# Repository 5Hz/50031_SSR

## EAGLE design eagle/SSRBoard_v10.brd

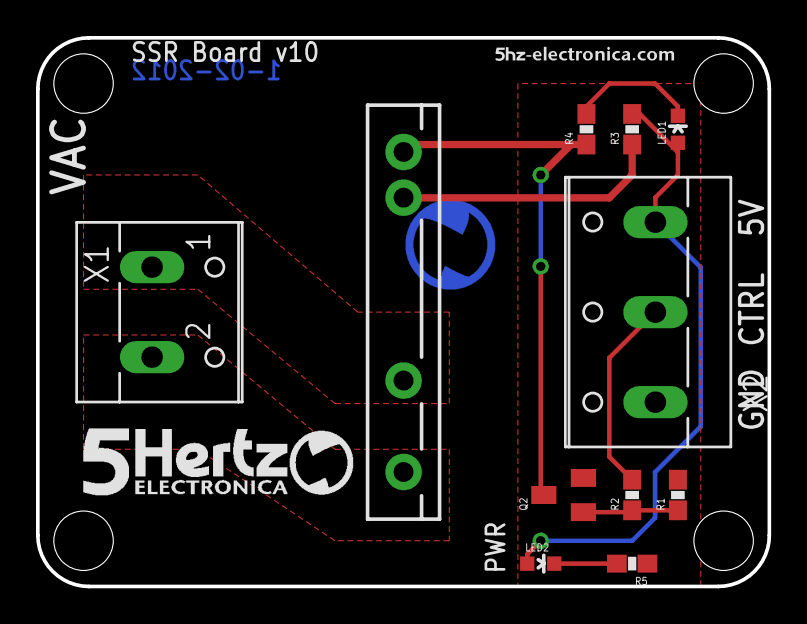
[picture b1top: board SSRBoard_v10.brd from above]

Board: 2 copper layers, 40.6 x 30.5 mm, 18 parts (1 on the bottom side), 10 nets.

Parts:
LED1, LED2: LED-0603
LOGO1: LOGO_5HZ_H_15MM; 5HZ_LOGO_H_15MM
LOGO2: LOGO_5HZ_WEB_COOPER_10MM; 5HZ_WEB_COOPER_10MM
LOGO4: LOGO_5HZ_CIRC_COOPER_5MM; 5HZ_LOGO_CIRC_COOPER_5MM
Q2: 2N3904; SOT23
R1: 10K; 0603-RES
R2, R4, R5: 330; 0603-RES
R3: 150; 0603-RES
U1: S108T02; RELAY-S108T02
U$3, U$4, U$5, U$7: STAND-OFF
X1: W237-102
X2: W237-103

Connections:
5V: LED1.A, LED2.A, R3.2, X2.3
COIL: Q2.3, R4.1, U1.4
CTL: R2.2, X2.2
GND: Q2.2, R1.2, R5.1, X2.1
LOAD1: U1.1, X1.2
LOAD2: U1.2, X1.1
unnamed: R3.1, U1.3
unnamed: LED2.C, R5.2
unnamed: Q2.1, R1.1, R2.1
unnamed: LED1.C, R4.2

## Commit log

2014-01-10 creación
